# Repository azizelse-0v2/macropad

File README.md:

# Macro Pad

A custom macro pad featuring 4 mechanical switches, a rotary encoder, OLED display, and RGB LEDs. Built with the Seeed XIAO RP2040 microcontroller and KMK firmware for a compact, programmable keyboard solution.

## Features

- **4 Cherry MX Switches**: Tactile mechanical switches for responsive key presses
- **Rotary Encoder**: For volume control or custom macros
- **0.96" OLED Display**: SH1106 I2C display for status or custom graphics
- **RGB LED Matrix**: WS2812B LEDs for visual feedback
- **Compact Design**: Fits within 200x200x100mm enclosure
- **KMK Firmware**: Python-based firmware for easy customization

## Images

### Schematic

### PCB Layout

### Case Assembly

## Bill of Materials (BOM)

| Part | Quantity | Description | Supplier |
|------|----------|-------------|----------|
| Seeed XIAO RP2040 | 1 | RP2040 microcontroller board | Seeed Studio |
| Cherry MX Switch | 4 | Mechanical keyboard switches | Cherry |
| DSA Keycap | 4 | Cherry MX compatible keycaps | Keycaps Direct |
| 0.96" OLED Display | 1 | SH1106 128x64 I2C OLED | AliExpress |
| Rotary Encoder | 1 | EC11 rotary encoder | AliExpress |
| WS2812B LED | 4 | RGB LEDs | AliExpress |
| Custom PCB | 1 | 2-layer PCB | This project |
| 3D Printed Case | 1 | ABS/PLA case parts | This project |

## Project Structure

```
macro_pad/
├── CAD/                 # 3D models and assembly
│   ├── macro_pad.step   # Complete assembly model
│   └── Pictures/        # Rendered images
├── PCB/                 # KiCAD design files
│   ├── macro_pad.kicad_pro
│   ├── macro_pad.kicad_sch
│   ├── macro_pad.kicad_pcb
│   └── Pictures/        # PCB images
├── Firmware/            # KMK firmware source
│   ├── main.py
│   └── kmk/             # KMK library
├── Production/          # Manufacturing files
│   ├── gerbers.zip      # PCB gerbers
│   ├── Top.STL          # Case parts
│   ├── Bottom.STL
│   └── firmware.uf2     # Compiled firmware
└── README.md
```

## Building the Macro Pad

### PCB Manufacturing
1. Download `Production/gerbers.zip`
2. Upload to your preferred PCB manufacturer (JLCPCB, PCBWay, etc.)
3. Order 2-layer PCBs with standard specifications

### Case Printing
1. Use the STL files in `Production/` for 3D printing
2. Print with ABS or PLA, 0.2mm layer height recommended
3. Assemble with M2/M3 screws

### Assembly
1. Solder components to the PCB
2. Mount switches and encoder
3. Connect OLED and LEDs
4. Place PCB in case and secure

### Firmware Flashing
1. Install KMK firmware (see Firmware/ directory)
2. Put XIAO RP2040 into bootloader mode (double-click reset)
3. Drag `firmware.uf2` to the RPI-RP2 drive

## Customization

The firmware is written in Python using KMK. Edit `Firmware/main.py` to customize key mappings, LED effects, and display output.

## Repository

- **GitHub**: [azizelse/macro_pad](https://github.com/azizelse/macro_pad)
- **License**: MIT

## Acknowledgments

This project is submitted as part of the Hackpad community challenge. Special thanks to the KMK firmware developers and the open-source hardware community.

---

*Built with ❤️ using KiCAD, Fusion 360, and KMK*

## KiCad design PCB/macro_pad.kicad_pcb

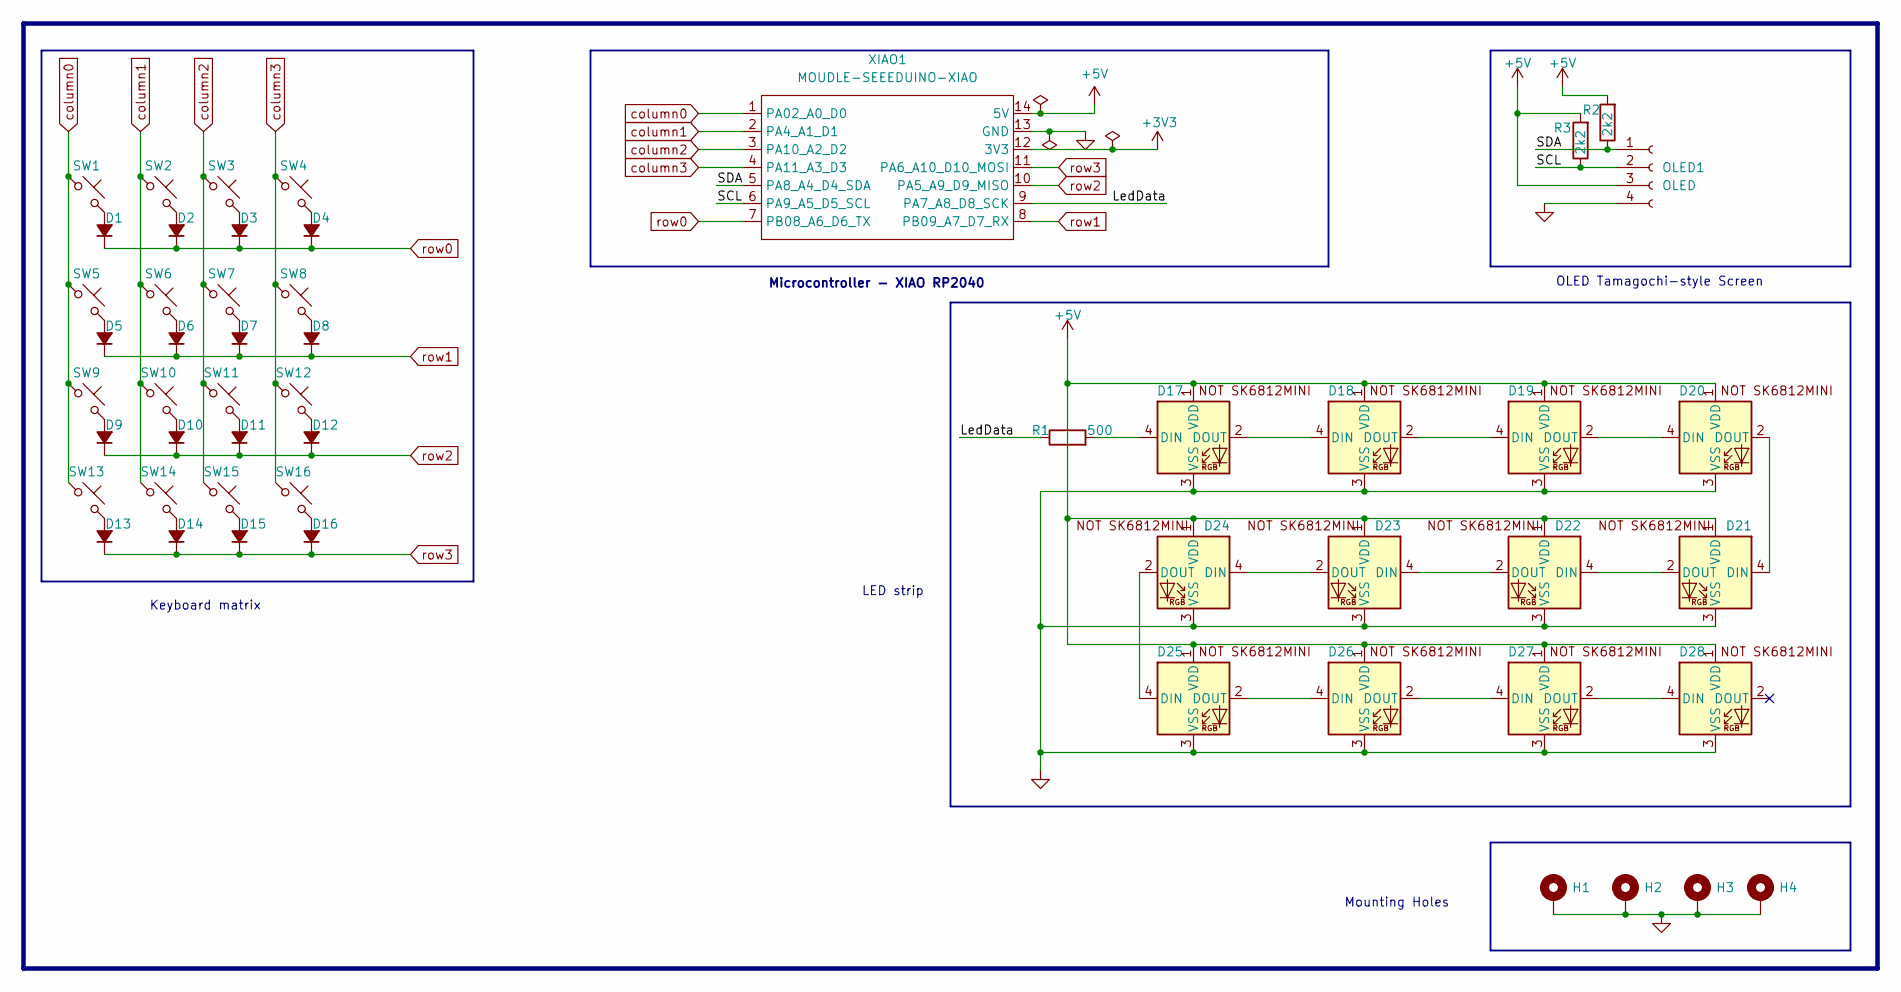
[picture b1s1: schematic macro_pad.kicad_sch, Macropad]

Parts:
D1, D2, D3, D4, D5, D6, D7, D8, D9, D10, D11, D12, D13, D14, D15, D16: D_Small_Filled; D_DO-35_SOD27_P7.62mm_Horizontal
D17, D18, D19, D20, D21, D22, D23, D24, D25, D26, D27, D28: SK6812MINI-E; SK6812MINI-E_fixed
H1, H2, H3, H4: MountingHole_Pad; MountingHole_3.2mm_M3_ISO7380_Pad
OLED1: OLED; PinSocket_1x04_P2.54mm_Vertical
R1: 500; R_Axial_DIN0204_L3.6mm_D1.6mm_P7.62mm_Horizontal
R2, R3: 2k2; R_Axial_DIN0204_L3.6mm_D1.6mm_P7.62mm_Horizontal
SW1, SW2, SW3, SW4, SW5, SW6, SW7, SW8, SW9, SW10, SW11, SW12, SW13, SW14, SW15, SW16: SW_Push_45deg; SW_Cherry_MX_1.00u_PCB
XIAO1: MOUDLE-SEEEDUINO-XIAO; XIAO_RP2040

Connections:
+3V3: XIAO1.12 (3V3)
+5V: D17.1 (VDD), D18.1 (VDD), D19.1 (VDD), D20.1 (VDD), D21.1 (VDD), D22.1 (VDD), D23.1 (VDD), D24.1 (VDD), D25.1 (VDD), D26.1 (VDD), D27.1 (VDD), D28.1 (VDD), OLED1.3, R2.2, R3.2, XIAO1.14 (5V)
/LedData: R1.1, XIAO1.9 (PA7_A8_D8_SCK)
/SCL: OLED1.2, R3.1, XIAO1.6 (PA9_A5_D5_SCL)
/SDA: OLED1.1, R2.1, XIAO1.5 (PA8_A4_D4_SDA)
GND: D17.3 (VSS), D18.3 (VSS), D19.3 (VSS), D20.3 (VSS), D21.3 (VSS), D22.3 (VSS), D23.3 (VSS), D24.3 (VSS), D25.3 (VSS), D26.3 (VSS), D27.3 (VSS), D28.3 (VSS), H1.1, H2.1, H3.1, H4.1, OLED1.4, XIAO1.13 (GND)
unnamed: D1.2 (A), SW1.2
unnamed: D2.2 (A), SW2.2
unnamed: D3.2 (A), SW3.2
unnamed: D4.2 (A), SW4.2
unnamed: D5.2 (A), SW5.2
unnamed: D6.2 (A), SW6.2
unnamed: D7.2 (A), SW7.2
unnamed: D8.2 (A), SW8.2
unnamed: D9.2 (A), SW9.2
unnamed: D10.2 (A), SW10.2
unnamed: D11.2 (A), SW11.2
unnamed: D12.2 (A), SW12.2
unnamed: D13.2 (A), SW13.2
unnamed: D14.2 (A), SW14.2
unnamed: D15.2 (A), SW15.2
unnamed: D16.2 (A), SW16.2
unnamed: D17.4 (DIN), R1.2
unnamed: D17.2 (DOUT), D18.4 (DIN)
unnamed: D18.2 (DOUT), D19.4 (DIN)
unnamed: D19.2 (DOUT), D20.4 (DIN)
unnamed: D20.2 (DOUT), D21.4 (DIN)
unnamed: D21.2 (DOUT), D22.4 (DIN)
unnamed: D22.2 (DOUT), D23.4 (DIN)
unnamed: D23.2 (DOUT), D24.4 (DIN)
unnamed: D24.2 (DOUT), D25.4 (DIN)
unnamed: D25.2 (DOUT), D26.4 (DIN)
unnamed: D26.2 (DOUT), D27.4 (DIN)
unnamed: D27.2 (DOUT), D28.4 (DIN)
column0: SW1.1, SW5.1, SW9.1, SW13.1, XIAO1.1 (PA02_A0_D0)
column1: SW2.1, SW6.1, SW10.1, SW14.1, XIAO1.2 (PA4_A1_D1)
column2: SW3.1, SW7.1, SW11.1, SW15.1, XIAO1.3 (PA10_A2_D2)
column3: SW4.1, SW8.1, SW12.1, SW16.1, XIAO1.4 (PA11_A3_D3)
row0: D1.1 (K), D2.1 (K), D3.1 (K), D4.1 (K), XIAO1.7 (PB08_A6_D6_TX)
row1: D5.1 (K), D6.1 (K), D7.1 (K), D8.1 (K), XIAO1.8 (PB09_A7_D7_RX)
row2: D9.1 (K), D10.1 (K), D11.1 (K), D12.1 (K), XIAO1.10 (PA5_A9_D9_MISO)
row3: D13.1 (K), D14.1 (K), D15.1 (K), D16.1 (K), XIAO1.11 (PA6_A10_D10_MOSI)

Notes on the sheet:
Microcontroller - XIAO RP2040
Keyboard matrix
LED strip
Mounting Holes
OLED Tamagochi-style Screen

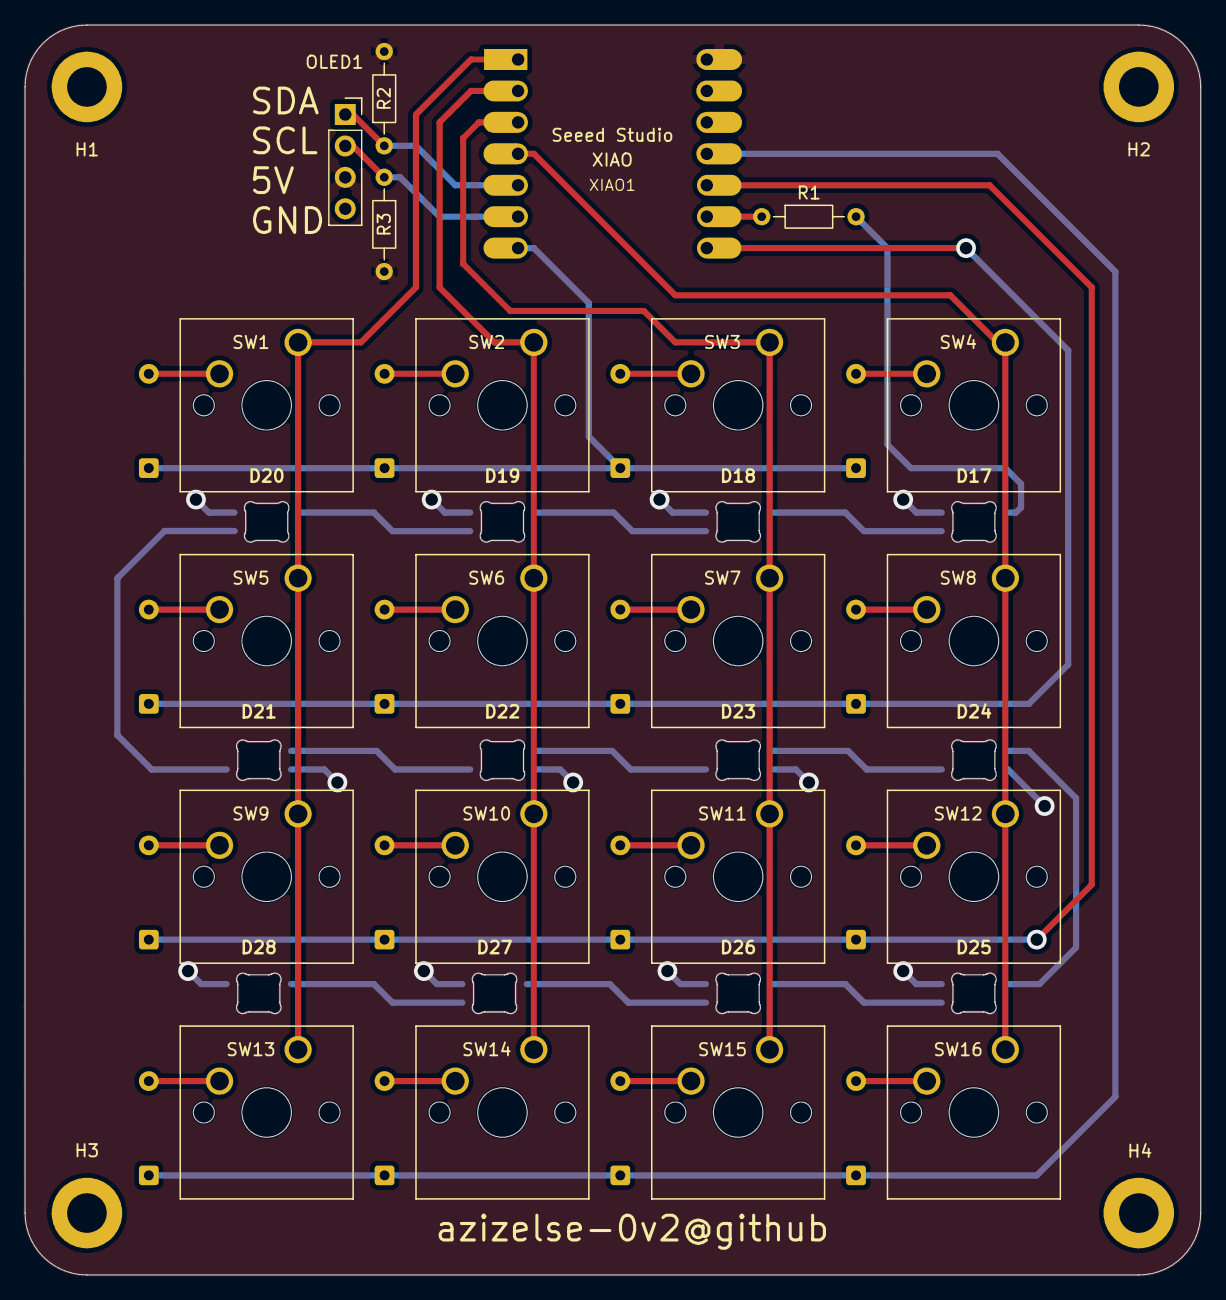
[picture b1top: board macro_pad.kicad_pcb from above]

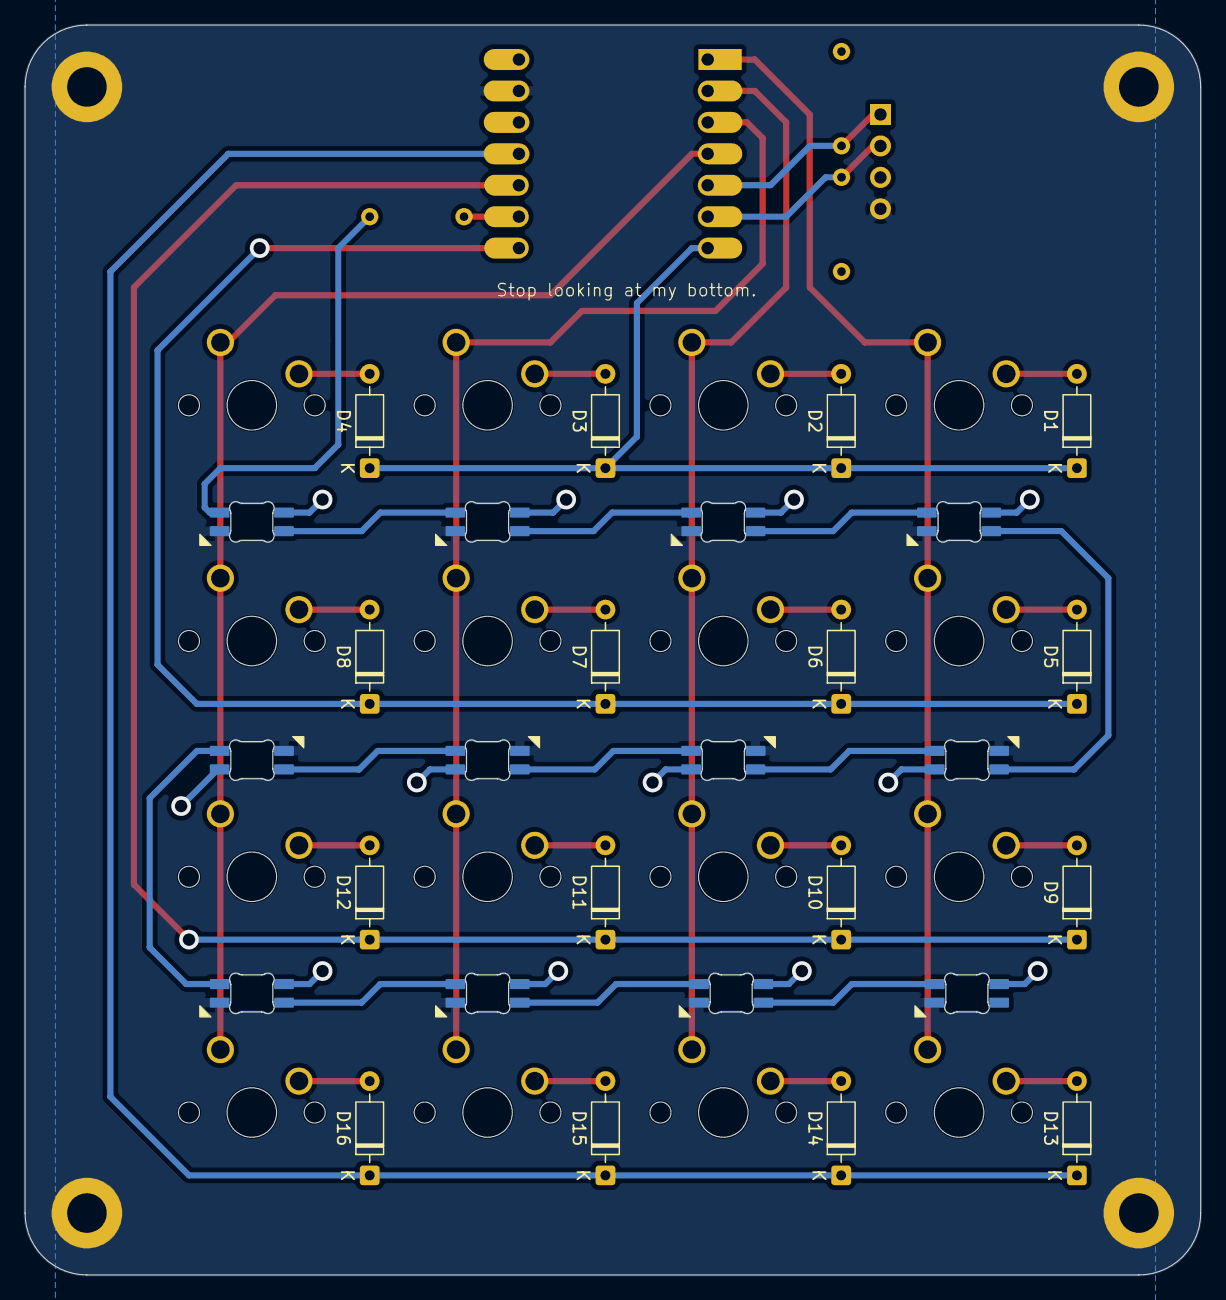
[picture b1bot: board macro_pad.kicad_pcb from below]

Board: 2 copper layers, 95.0 x 100.9 mm, 53 parts (16 on the bottom side), 41 nets.

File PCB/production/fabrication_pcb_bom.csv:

Designator,Footprint,Quantity,Value,LCSC Part #
"D1, D10, D11, D12, D13, D14, D15, D16, D2, D3, D4, D5, D6, D7, D8, D9",D_DO-35_SOD27_P7.62mm_Horizontal,16,D_Small_Filled,
"D17, D18, D19, D20, D21, D22, D23, D24, D25, D26, D27, D28",SK6812MINI-E_fixed,12,SK6812MINI-E,
OLED1,PinSocket_1x04_P2.54mm_Vertical,1,OLED,
R1,R_Axial_DIN0204_L3.6mm_D1.6mm_P7.62mm_Horizontal,1,500,
"R2, R3",R_Axial_DIN0204_L3.6mm_D1.6mm_P7.62mm_Horizontal,2,2k2,
"SW1, SW10, SW11, SW12, SW13, SW14, SW15, SW16, SW2, SW3, SW4, SW5, SW6, SW7, SW8, SW9",SW_Cherry_MX_1.00u_PCB,16,SW_Push_45deg,
XIAO1,XIAO_RP2040,1,MOUDLE-SEEEDUINO-XIAO,

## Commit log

2026-03-01 Improved design
2026-03-03 Added mounting holes
2026-03-03 Uploaded firmware and removed backups
2026-03-04 Added Frame and Firmware
2026-03-04 Added git-lfs
2026-03-04 Modified Frame
2026-03-04 Removed large assets
2026-03-12 Modified frame & schem
2026-03-15 Followed guidelines on schem
2026-03-15 Changed Microcontroller and size of pcb
2026-03-15 Finalised CAD
2026-03-15 Added README.md and pictures
2026-03-15 Copilot generated README
2026-03-15 Updated README and added extra photos
2026-03-15 Add MIT License to the project
2026-03-15 Removed unnecessary firmware files and generated pcb production files
2026-03-16 Added firmware to production files
2026-03-17 Zip files are tracked now
2026-05-02 Finalized everything
